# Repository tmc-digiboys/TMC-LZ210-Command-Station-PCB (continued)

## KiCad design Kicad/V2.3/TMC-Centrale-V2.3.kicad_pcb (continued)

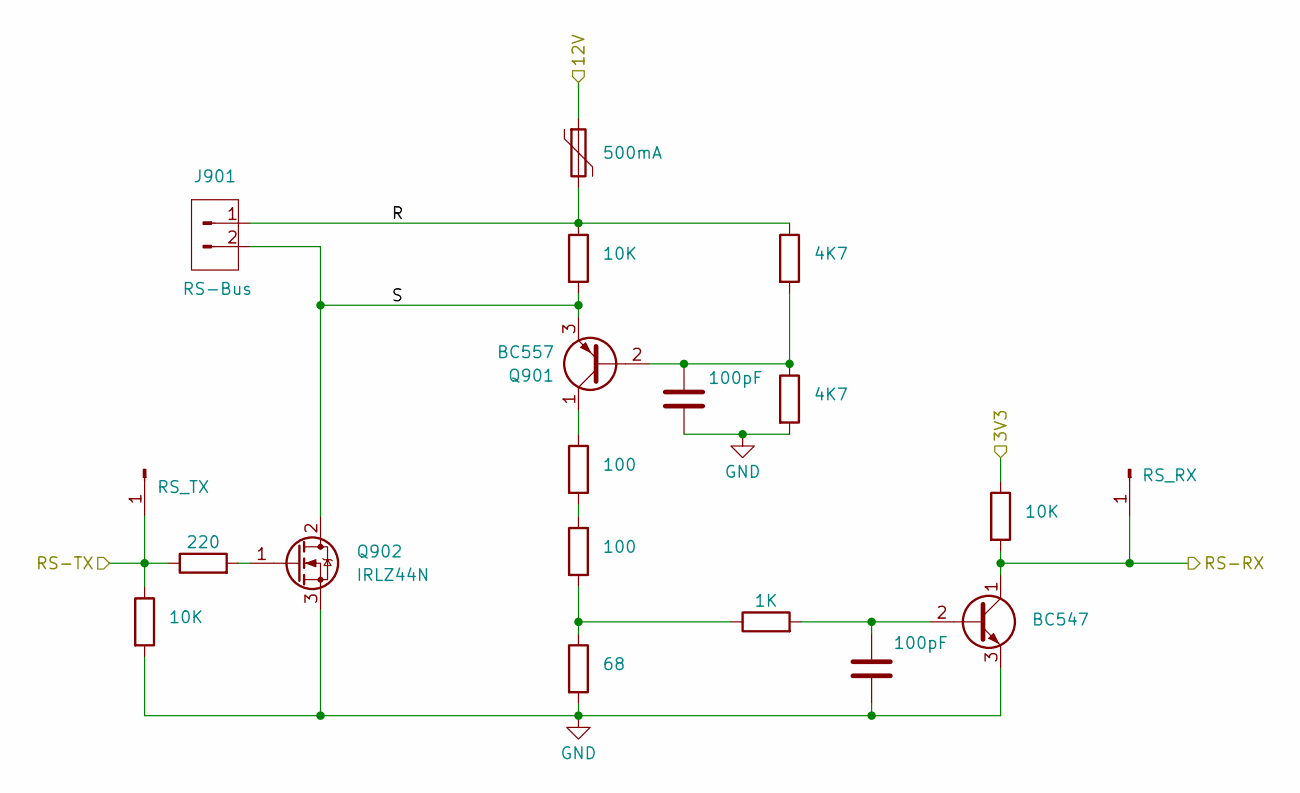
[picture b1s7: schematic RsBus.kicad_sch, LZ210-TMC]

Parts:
C901, C902: 100pF; C_Disc_D8.0mm_W2.5mm_P5.00mm
F901: 500mA; Fuse_Bourns_MF-RHT050
J901: RS-Bus; PhoenixContact_MC_1,5_2-G-3.81_1x02_P3.81mm_Horizontal
J902: RS_TX; PinHeader_1x01_P2.54mm_Vertical
J903: RS_RX; PinHeader_1x01_P2.54mm_Vertical
Q901: BC557; TO-92_BC5xx_HandSolder
Q902: IRLZ44N; TO-220-3_Vertical
Q903: BC547; TO-92_BC5xx_HandSolder
R901, R905, R908: 10K; R-0207-10
R902, R903: 4K7; R-0207-10
R904, R906: 100; R-0207-10
R907: 220; R-0207-10
R909: 1K; R-0207-10
R910: 68; R-0207-10

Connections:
/3V3: R905.1; also elsewhere on the board
/12V: F901.1; also elsewhere on the board
/MCU/RS-RX: J903.1 (Pin_1_1), Q903.1 (C), R905.2; also elsewhere on the board
/MCU/RS-TX: J902.1 (Pin_1_1), R907.1, R908.1; also elsewhere on the board
/RsBus/R: F901.2, J901.1, R901.1, R902.1
/RsBus/S: J901.2, Q901.3 (E), Q902.2 (D), R901.2
GND: C901.2, C902.2, Q902.3 (S), Q903.3 (E), R903.2, R908.2, R910.2; also elsewhere on the board
unnamed: C901.1, Q901.2 (B), R902.2, R903.1
unnamed: Q901.1 (C), R904.1
unnamed: Q902.1 (G), R907.2
unnamed: C902.1, Q903.2 (B), R909.2
unnamed: R904.2, R906.1
unnamed: R906.2, R909.1, R910.1

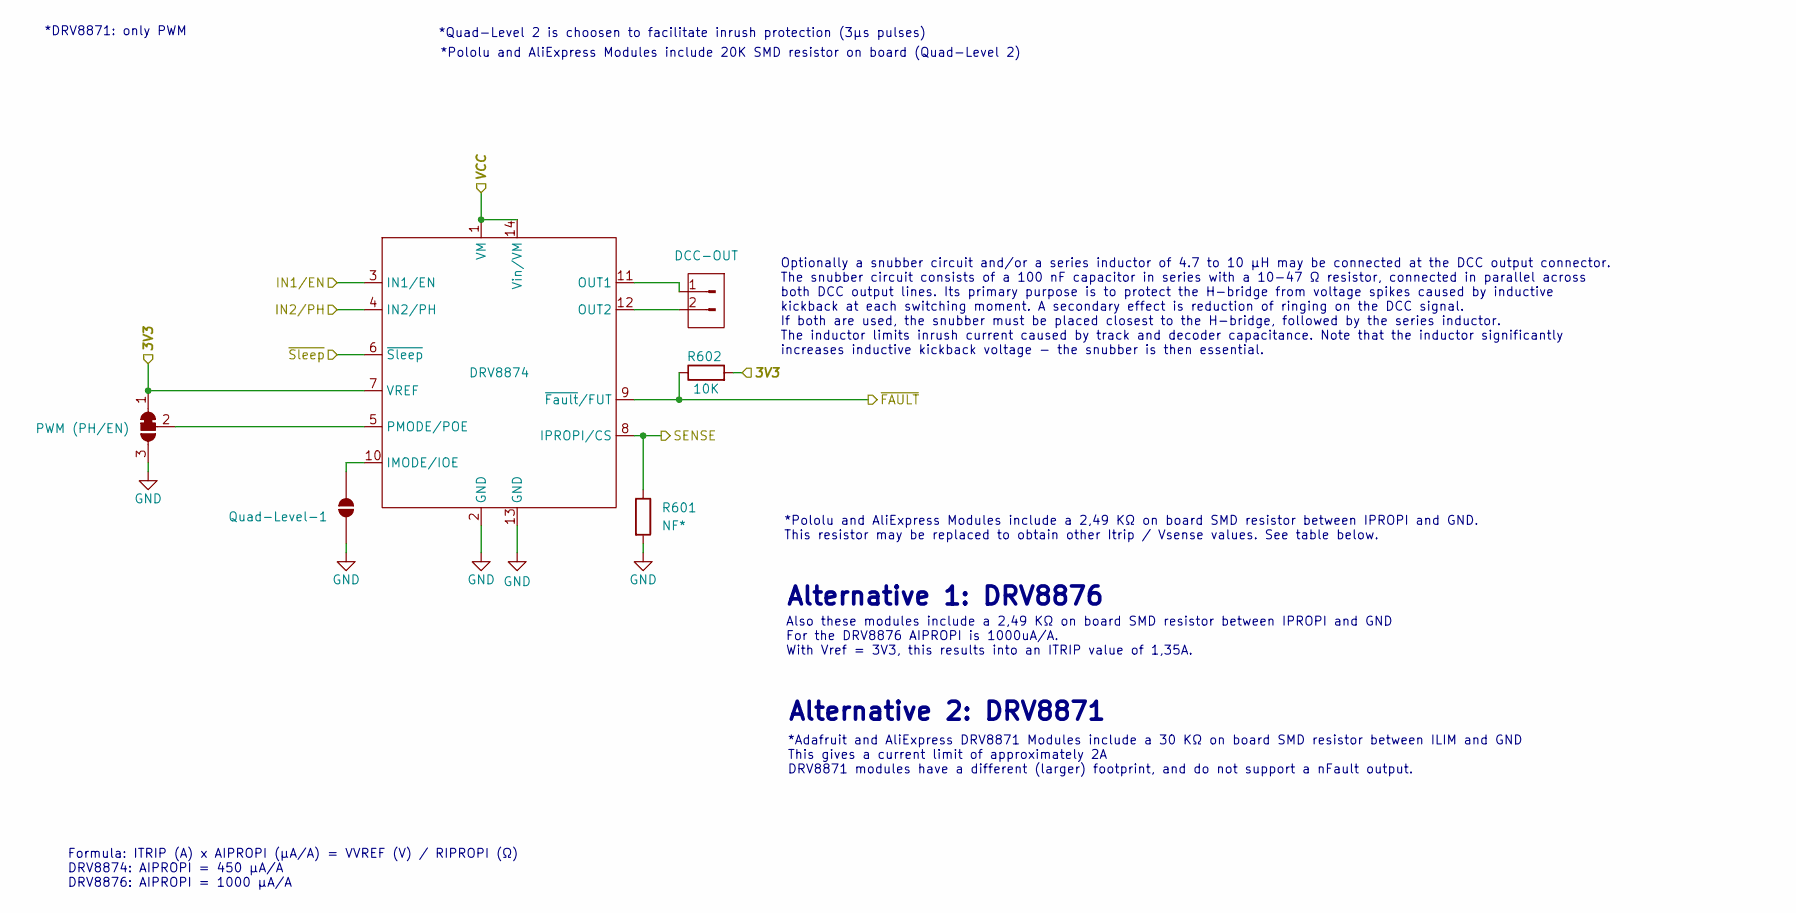
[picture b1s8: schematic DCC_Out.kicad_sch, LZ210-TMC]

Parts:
J601: DCC-OUT; PhoenixContact_MSTBA_2,5_2-G_1x02_P5.00mm_Horizontal
JP601: PWM (PH/EN); SolderJumper-3_P1.3mm_Bridged12_RoundedPad1.0x1.5mm_NumberL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
JP602: Quad-Level-1; SolderJumper-2_P1.3mm_Open_RoundedPad1.0x1.5mm
R601: NF*; R-0207-10
R602: 10K; R-0207-10
U601: DRV8874; Module-DRV8874

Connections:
/3V3: JP601.1 (A), R602.2, U601.7 (VREF); also elsewhere on the board
/CDE-Interface/IN1/EN: U601.3 (IN1/EN); also elsewhere on the board
/CDE-Interface/IN2/PH: U601.4 (IN2/PH); also elsewhere on the board
/DCC-Out/SENSE: R601.1, U601.8 (IPROPI/CS); also elsewhere on the board
/DCC-Out/~FAULT: R602.1, U601.9 (~Fault/FUT); also elsewhere on the board
/DCC-Out/~Sleep: U601.6 (~Sleep); also elsewhere on the board
/VCC: U601.1 (VM), U601.14 (Vin/VM); also elsewhere on the board
GND: JP601.3 (B), JP602.1 (A), R601.2, U601.2 (GND), U601.13 (GND); also elsewhere on the board
unnamed: J601.1, U601.11 (OUT1)
unnamed: J601.2, U601.12 (OUT2)
unnamed: JP601.2 (C), U601.5 (PMODE/POE)
unnamed: JP602.2 (B), U601.10 (IMODE/IOE)

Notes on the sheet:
*Pololu and AliExpress Modules include 20K SMD resistor on board (Quad-Level 2)
Alternative 2: DRV8871
*Quad-Level 2 is choosen to facilitate inrush protection (3µs pulses)
Alternative 1: DRV8876
*Adafruit and AliExpress DRV8871 Modules include a 30 KΩ on board SMD resistor between ILIM and GND This gives a current limit of approximately 2A DRV8871 modules have a different (larger) footprint, and do not support a nFault output.
Formula: ITRIP (A) x AIPROPI (μA/A) = VVREF (V) / RIPROPI (Ω) DRV8874: AIPROPI = 450 μA/A DRV8876: AIPROPI = 1000 μA/A
Also these modules include a 2,49 KΩ on board SMD resistor between IPROPI and GND For the DRV8876 AIPROPI is 1000uA/A. With Vref = 3V3, this results into an ITRIP value of 1,35A.
*DRV8871: only PWM
*Pololu and AliExpress Modules include a 2,49 KΩ on board SMD resistor between IPROPI and GND. This resistor may be replaced to obtain other Itrip / Vsense values. See table below.
Optionally a snubber circuit and/or a series inductor of 4.7 to 10 µH may be connected at the DCC output connector. The snubber circuit consists of a 100 nF capacitor in series with a 10-47 Ω resistor, connected in parallel across both DCC output lines. Its primary purpose is to protect the H-bridg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

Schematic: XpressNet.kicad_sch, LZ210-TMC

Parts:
C501: 100nF; C_Disc_D5.0mm_W2.5mm_P2.50mm
F501: Polyfuse 500mA; Fuse_Bourns_MF-RHT050
J501: DIN-XpressNet; Connector-DIN-XpressNet
J502: XPN; PinHeader_1x03_P2.54mm_Vertical
J503: XpressNet; PhoenixContact_MC_1,5_4-G-3.81_1x04_P3.81mm_Horizontal
R501, R503: 560; R-0207-10
R502: 120; R-0207-10
R504: 8K2; R-0207-10
U501: MAX3485; DIL08

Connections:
/3V3: C501.1, R501.2, U501.8 (VCC); also elsewhere on the board
/12V: F501.2; also elsewhere on the board
/MCU/XpressNetRX: J502.3, U501.1 (RO); also elsewhere on the board
/MCU/XpressNetS/R: J502.2, R504.1, U501.2 (~RE), U501.3 (DE); also elsewhere on the board
/MCU/XpressNetTX: J502.1, U501.4 (DI); also elsewhere on the board
/XpressNet/A: J501.4, J503.3, R501.1, R502.2, U501.6 (A)
/XpressNet/B: J501.5, J503.4, R502.1, R503.2, U501.7 (B)
GND: C501.2, J501.3, J501.6, J501.7, J503.2, R503.1, R504.2, U501.5 (GND); also elsewhere on the board
unnamed: F501.1, J501.1, J503.1

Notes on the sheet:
The MAX3483 is a slewrate limited equivalent of the MAX3485 (250kBit instead of 2.5 MBit). Lower slewrate results in a cleaner XpressNet signal (less ringing). The DIP-8 version of the MAX3483 is relatively expensive, however.
The SMD variant of this board may use an SM712 Asymmerical TVS Diode for RS-485 protection.

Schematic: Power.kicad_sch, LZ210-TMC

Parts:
C301: 470uF; CP_Radial_D10.0mm_P5.00mm
D301: 1N5822; D_DO-201AD_P15.24mm_Horizontal
D302: D; Module-XL74610
F301: Polyfuse; Fuse_Bourns_MF-RG300
J301, J302: GND; PinHeader_1x01_P2.54mm_Vertical
J303: Connector-Power-Barrel-Jack
U301: 5V Step down Module; Module-StepDown-MP1584-Formfactor
U302: 12V Step down Module; Module-StepDown-MP1584-Formfactor

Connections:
/5V: D301.1 (K); also elsewhere on the board
/12V: U302.3 (VOUT+); also elsewhere on the board
/Power/POW_IN_AFTER_FUSE: D302.2 (A), F301.2
/Power/POW_IN_FOR_FUSE: F301.1, J303.1
/VCC: C301.1, D302.1 (K), U301.1 (VIN+), U302.1 (VIN+); also elsewhere on the board
GND: C301.2, J301.1 (Pin_1_1), J302.1 (Pin_1_1), J303.2, J303.3, U301.2 (GND), U302.2 (GND); also elsewhere on the board
unnamed: D301.2 (A), U301.3 (VOUT+)

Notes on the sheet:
The Olimex RP2350-XL Module can not be powered from external 3V3, but requires external 5V. The Module has a TPS62A02, which can not be disabled since it has Active Output Discharge. Active Output Discharge connects the output via a resistor to GND. The extra diode is needed to protect against pote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

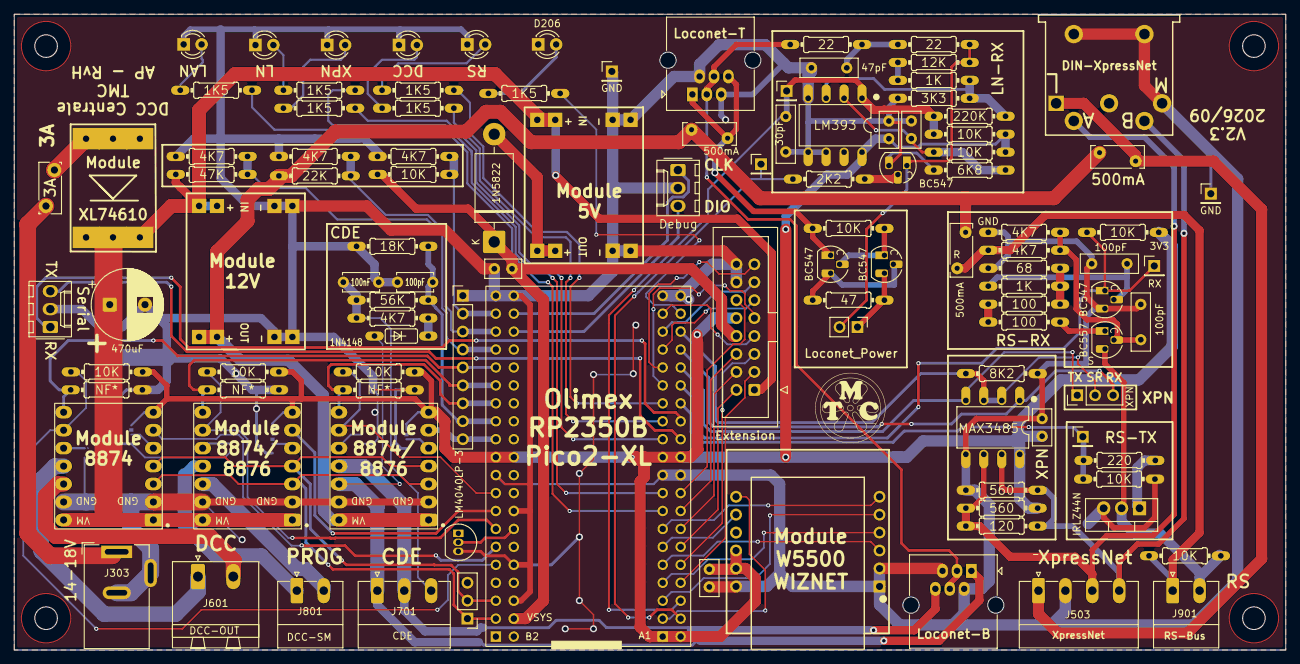
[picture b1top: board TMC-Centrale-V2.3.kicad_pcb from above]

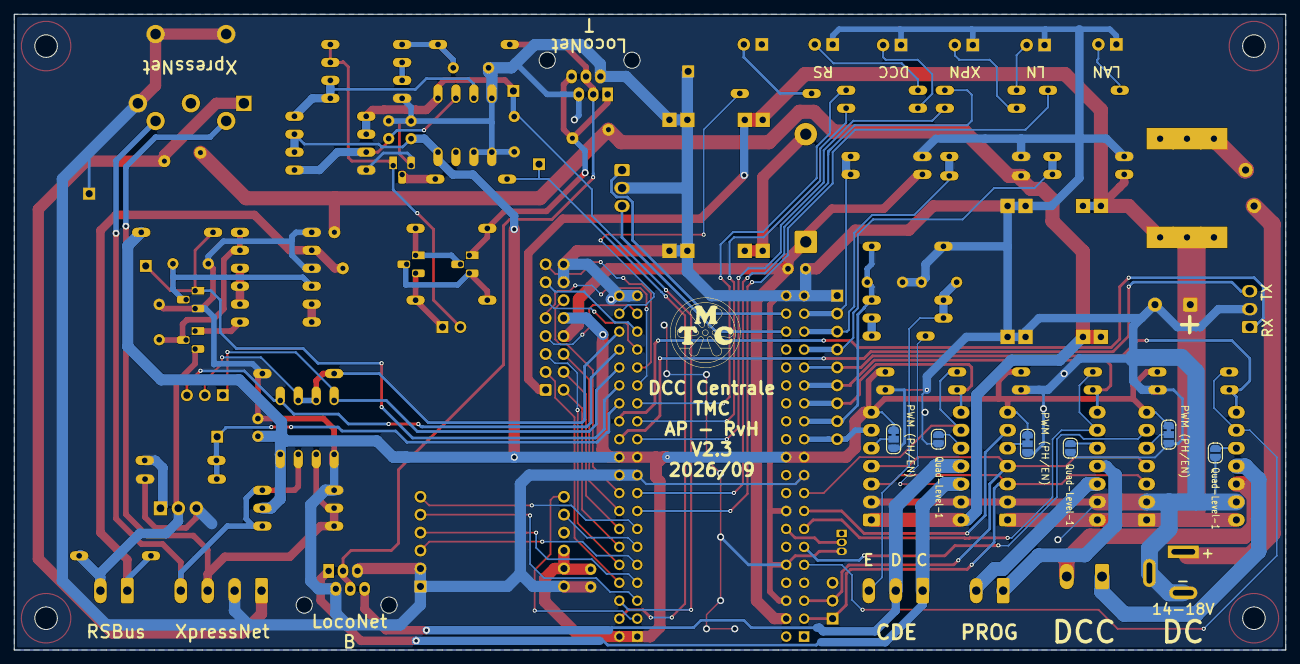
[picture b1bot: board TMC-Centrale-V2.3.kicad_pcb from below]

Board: 2 copper layers, 180.0 x 90.0 mm, 120 parts (6 on the bottom side), 100 nets.

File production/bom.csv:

Designator,Footprint,Quantity,Value,LCSC Part #
C1001,C_Disc_D8.0mm_W2.5mm_P5.00mm,1,47pF,
C1002,C_Disc_D8.0mm_W2.5mm_P5.00mm,1,30pF,
"C1003, C1004, C1005, C201, C401, C501",C_Disc_D5.0mm_W2.5mm_P2.50mm,6,100nF,
"C1006, C1007",C_Rect_L10.0mm_W5.0mm_P5.00mm_P7.50mm,2,"4,7nF",
C301,CP_Radial_D10.0mm_P5.00mm,1,470uF,
C701,C_Disc_D5.0mm_W2.5mm_P5.00mm,1,100nF,
C702,C_Disc_D5.0mm_W2.5mm_P5.00mm,1,100pF,
"C901, C902",C_Disc_D8.0mm_W2.5mm_P5.00mm,2,100pF,
D201,LED_D3.0mm,1,LAN,
D202,LED_D3.0mm,1,LN,
D203,LED_D3.0mm,1,XPN,
D204,LED_D3.0mm,1,DCC,
D205,LED_D3.0mm,1,RS,
D301,D_DO-201AD_P15.24mm_Horizontal,1,1N5822,
D302,Module-XL74610,1,D,
D701,DO35-7,1,1N4148,
"DTVS1001, DTVS1002",D_DO-15_P12.70mm_Horizontal,2,P6KE15A,
"F1001, F501",Fuse_Bourns_MF-RHT050,2,Polyfuse 500mA,
F301,Fuse_Bourns_MF-RG300,1,Polyfuse,
F901,Fuse_Bourns_MF-RHT050,1,500mA,
J1001,PinHeader_1x02_P2.54mm_Vertical,1,Loconet_Power,
J1002,RJ25_Wayconn_MJEA-660X1_Horizontal,1,Loconet-T,
J1003,PinHeader_1x01_P2.54mm_Vertical,1,LN_RX,
J1004,PinHeader_1x01_P2.54mm_Vertical,1,LN_TX,
J1005,PinHeader_1x01_P2.54mm_Vertical,1,LN_ACT,
J1006,RJ25_Wayconn_MJEA-660X1_Horizontal,1,Loconet-B,
J201,IDC-Header_2x08_P2.54mm_Vertical,1,Extension,
J202,Molex_KK-254_AE-6410-03A_1x03_P2.54mm_Vertical,1,Debug,
J203,Molex_KK-254_AE-6410-03A_1x03_P2.54mm_Vertical,1,Serial,
J204,PinHeader_1x03_P2.54mm_Vertical,1,DCC,
J205,PinHeader_1x09_P2.54mm_Vertical,1,Sense,
"J301, J302",PinHeader_1x01_P2.54mm_Vertical,2,GND,
J303,Connector-Power-Barrel-Jack,1,Connector-Power-Barrel-Jack,
J501,Connector-DIN-XpressNet,1,DIN-XpressNet,
J502,PinHeader_1x03_P2.54mm_Vertical,1,XPN,
J503,"PhoenixContact_MC_1,5_4-G-3.81_1x04_P3.81mm_Horizontal",1,XpressNet,
J601,"PhoenixContact_MSTBA_2,5_2-G_1x02_P5.00mm_Horizontal",1,DCC-OUT,
J701,"PhoenixContact_MC_1,5_3-G-3.81_1x03_P3.81mm_Horizontal",1,CDE,
J801,"PhoenixContact_MC_1,5_2-G-3.81_1x02_P3.81mm_Horizontal",1,DCC-SM,
J901,"PhoenixContact_MC_1,5_2-G-3.81_1x02_P3.81mm_Horizontal",1,RS-Bus,
J902,PinHeader_1x01_P2.54mm_Vertical,1,RS_TX,
J903,PinHeader_1x01_P2.54mm_Vertical,1,RS_RX,
"Q1001, Q1002, Q1003, Q903",TO-92_BC5xx_HandSolder,4,BC547,
Q901,TO-92_BC5xx_HandSolder,1,BC557,
Q902,TO-220-3_Vertical,1,IRLZ44N,
"R1001, R1005, R1006, R203, R602, R701, R802, R901, R905, R908",R-0207-10,10,10K,
R1002,R-0207-10,1,47,
"R1003, R1004",R-0207-10,2,22,
R1007,R-0207-10,1,12K,
R1008,R-0207-10,1,2K2,
"R1009, R909",R-0207-10,2,1K,
R1010,R-0207-10,1,220K,
R1011,R-0207-10,1,3K3,
R1012,R-0207-10,1,6K8,
"R1013, R1014",R_Axial_DIN0516_L15.5mm_D5.0mm_P20.32mm_Horizontal,2,33Ω (2W),
R201,R-0207-10,1,47K,
R202,R-0207-10,1,22K,
"R204, R205, R206, R207, R208",R-0207-10,5,1K5,
"R209, R210, R211, R703, R902, R903",R-0207-10,6,4K7,
"R501, R503",R-0207-10,2,560,
R502,R-0207-10,1,120,
R504,R-0207-10,1,8K2,
"R601, R702, R801",R-0207-10,3,NF*,
R704,R-0207-10,1,56K,
R705,R-0207-10,1,18K,
"R904, R906",R-0207-10,2,100,
R907,R-0207-10,1,220,
R910,R-0207-10,1,68,
U1001,DIL08,1,LM393,
U1002,DIL08,1,UCC27425,
U201,Module-RP2350B-XXL-Olimex,1,RaspberryPi_Pico2_Module-RP2350B-XXL-Olimex,
U202,TO-92_Inline,1,LM4040LP-3,
U301,Module-StepDown-MP1584-Formfactor,1,5V Step down Module,
U302,Module-StepDown-MP1584-Formfactor,1,12V Step down Module,
U401,Module-W5500,1,Module-W5500,
U501,DIL08,1,MAX3485,
U601,Module-DRV8874,1,DRV8874,
U701,Module-DRV8874,1,DRV8876,
U801,Module-DRV8874,1,DRV8874/8876,
